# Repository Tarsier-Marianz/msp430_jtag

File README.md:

A simple MSP430-JTAG Parallel Port Programmer

> Schematic image can be found inside **msp430_jtag** folder or click [here](https://github.com/Tarsier-Marianz/msp430_jtag/blob/master/msp430_jtag.sch.svg)

### Thanks

[KiCad IDE](http://kicad.org/) - for letting me use a free software in designing PCB

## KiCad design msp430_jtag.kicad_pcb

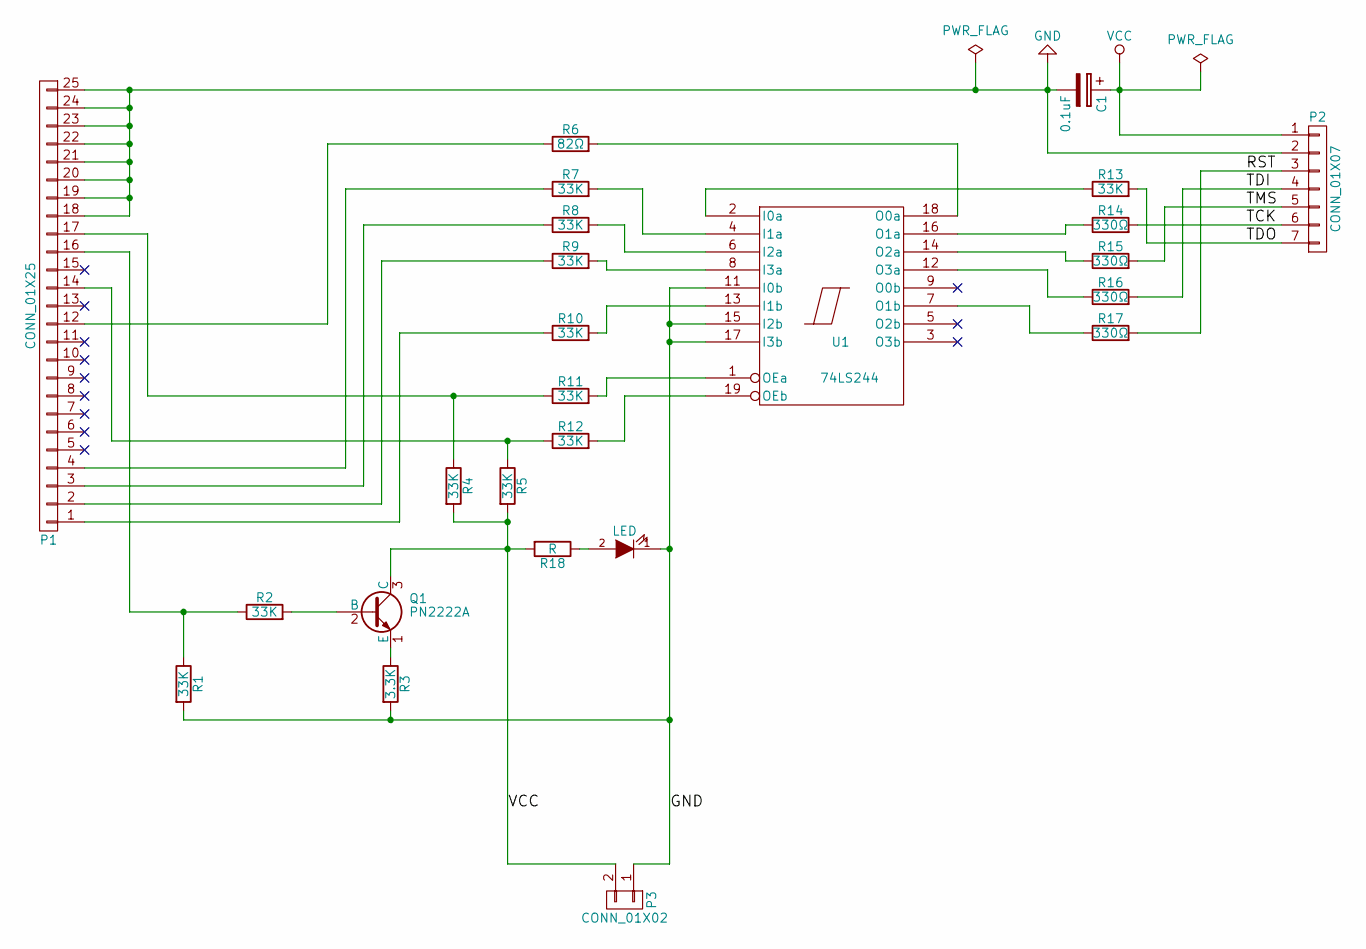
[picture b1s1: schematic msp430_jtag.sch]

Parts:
C1: 0.1uF; CP_Elec_3x5.3
D1: LED; LED_D3.0mm
P1: CONN_01X25; DB25F_CI
P2: CONN_01X07; TerminalBlock_4UCON_19963_07x3.5mm_Straight
P3: CONN_01X02; Harwin_LTek-Male_02x2.00mm_Straight
Q1: PN2222A; TO-92_Molded_Narrow
R1, R2, R4, R5, R7, R8, R9, R10, R11, R12, R13: 33K; R_1210_HandSoldering
R3: 3.3K; R_1210_HandSoldering
R6: 82Ω; R_0805_HandSoldering
R14, R15, R16, R17: 330Ω; R_0805_HandSoldering
R18: R; R_0805_HandSoldering
U1: 74LS244; SOIC-20W_7.5x12.8mm_Pitch1.27mm

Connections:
/RST: P2.3, R17.2
/TCK: P2.6, R14.2
/TDI: P2.4, R16.2
/TDO: P2.7, R13.2
/TMS: P2.5, R15.2
GND: C1.2, D1.1 (K), P1.18, P1.19, P1.20, P1.21, P1.22, P1.23, P1.24, P1.25, P2.2, P3.1, R1.2, R3.2, U1.10 (GND), U1.11 (I0b), U1.15 (I2b), U1.17 (I3b)
unnamed: D1.2 (A), R18.1
unnamed: P1.1, R10.1
unnamed: P1.2, R9.1
unnamed: P1.3, R8.1
unnamed: P1.4, R7.1
unnamed: P1.12, R6.1
unnamed: P1.14, R5.1, R12.1
unnamed: P1.16, R1.1, R2.1
unnamed: P1.17, R4.1, R11.1
unnamed: Q1.1 (E), R3.1
unnamed: Q1.2 (B), R2.2
unnamed: R6.2, U1.18 (O0a)
unnamed: R7.2, U1.4 (I1a)
unnamed: R8.2, U1.6 (I2a)
unnamed: R9.2, U1.8 (I3a)
unnamed: R10.2, U1.13 (I1b)
unnamed: R11.2, U1.1 (OEa)
unnamed: R12.2, U1.19 (OEb)
unnamed: R13.1, U1.2 (I0a)
unnamed: R14.1, U1.16 (O1a)
unnamed: R15.1, U1.14 (O2a)
unnamed: R16.1, U1.12 (O3a)
unnamed: R17.1, U1.7 (O1b)
VCC: C1.1, P2.1, P3.2, Q1.3 (C), R4.2, R5.2, R18.2, U1.20 (VCC)

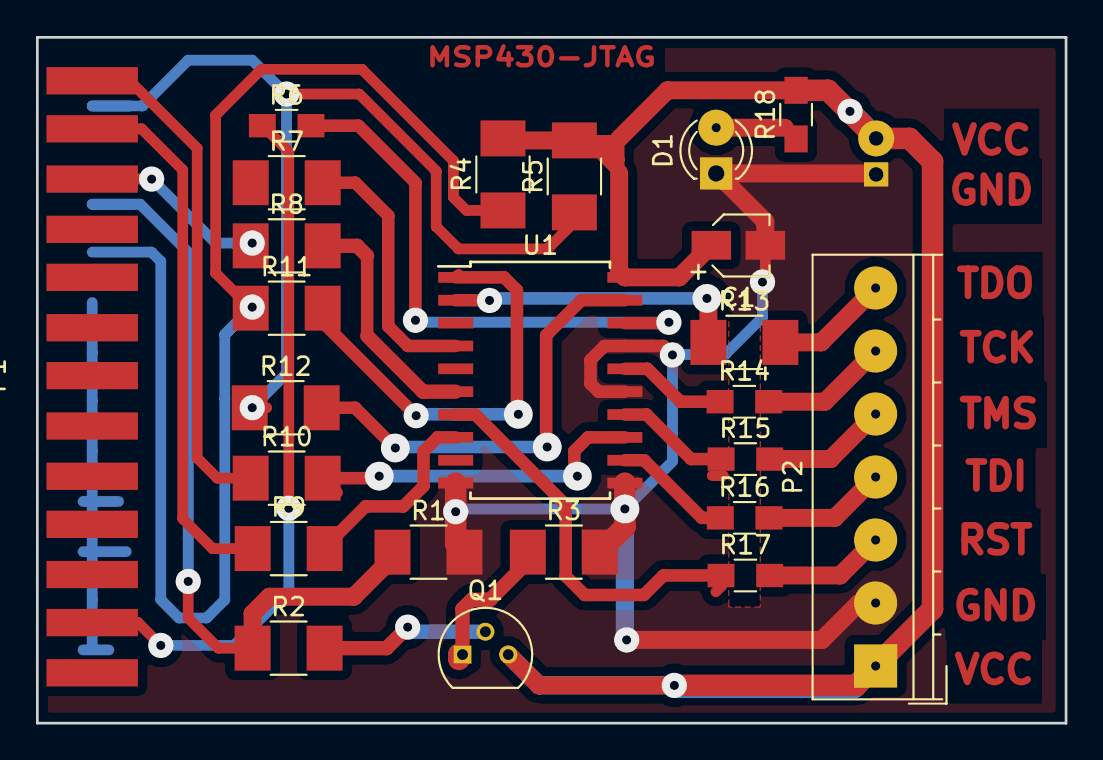
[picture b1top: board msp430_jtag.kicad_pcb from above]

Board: 2 copper layers, 57.2 x 38.1 mm, 25 parts (1 on the bottom side), 30 nets.

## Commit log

2018-03-13 + readme overview
2018-03-13 -duplicate image and + new
2018-03-13 *fixed 2 net-connection
2018-04-05 *change transistor footprint
2018-04-05 *change images from updated layout
2018-04-05 * readme with updated images
2018-11-07 *remapping symbols into latest version of kicad
2021-11-10 Update README.md
    https://forum.kicad.info/t/warning-avoid-all-links-to-kicad-pcb-org-use-kicad-org/31521
